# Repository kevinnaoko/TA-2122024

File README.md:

# TA-2122024
Capstone Design Kelompok 24

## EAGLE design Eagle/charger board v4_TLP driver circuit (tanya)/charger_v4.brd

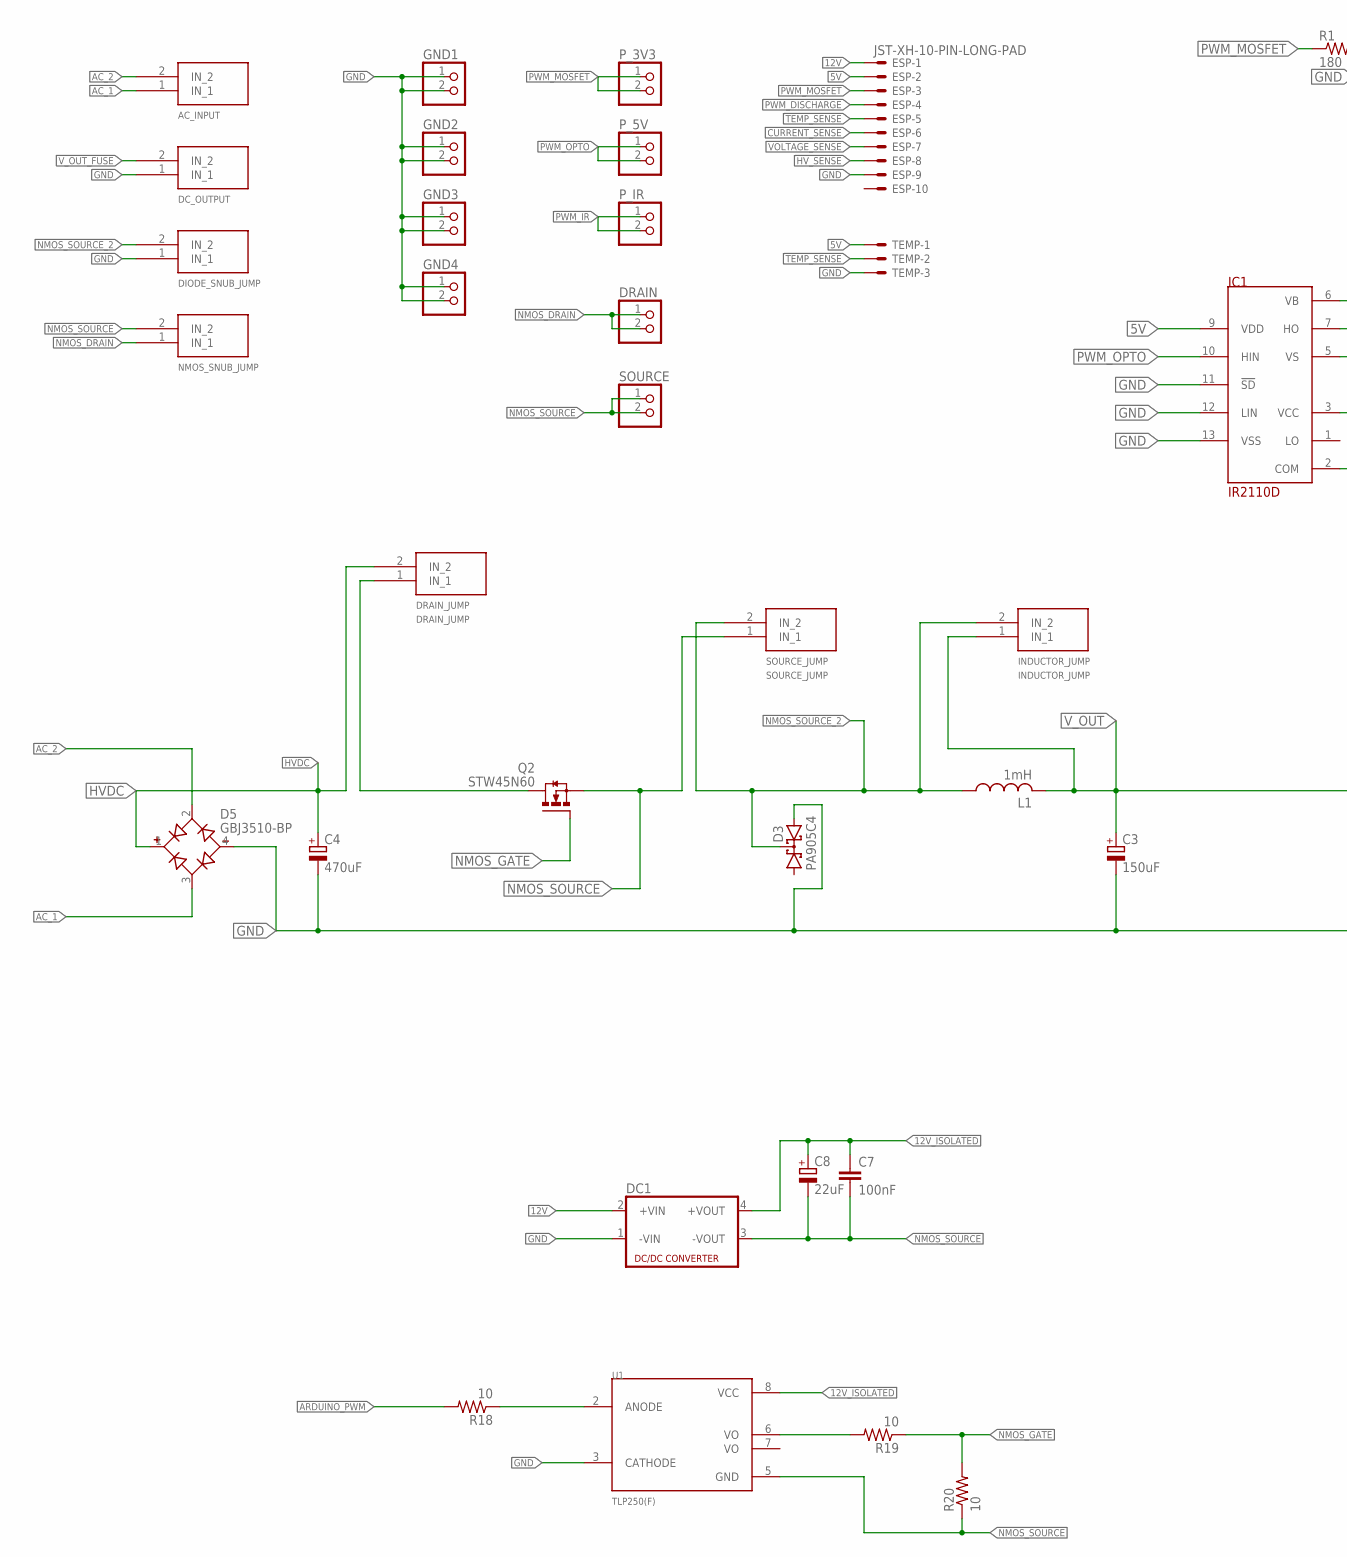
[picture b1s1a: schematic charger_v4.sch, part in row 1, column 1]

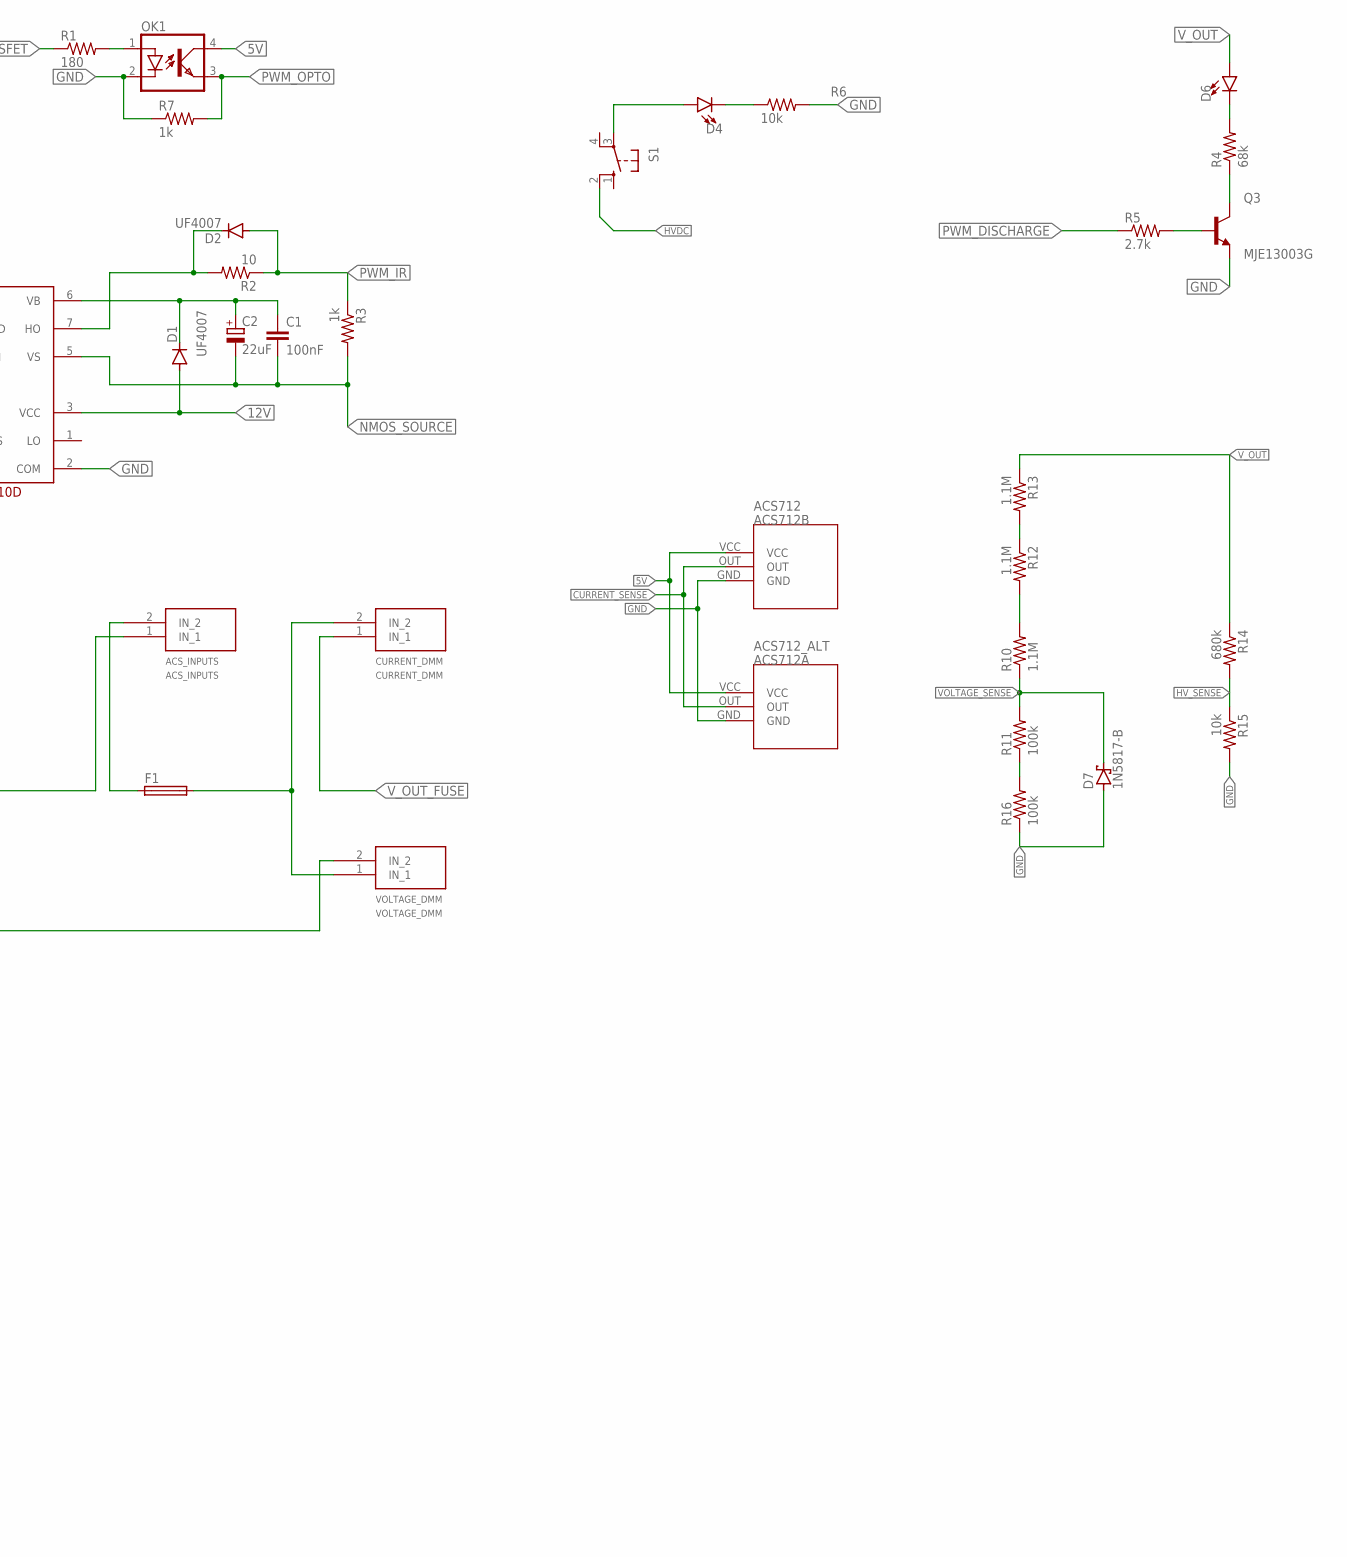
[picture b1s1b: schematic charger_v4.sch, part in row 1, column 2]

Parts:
ACS712: ACS712B; ACS712-2
ACS712_ALT: ACS712A; ACS712-1
ACS_INPUTS: ACS_INPUTS; TERMINAL_2P
AC_INPUT: AC_INPUT; TERMINAL_2P
C1, C7: 100nF; C025-025X050
C2, C8: 22uF; E2,5-6E
C3: 150uF; E7,5-18
C4: 470uF; EB35D
CURRENT_DMM: CURRENT_DMM; TERMINAL_2P
D1, D2: UF4007; DO34-7
D3: PA905C4; SOT93S
D4, D6: LED5MM; LED_5MM
D5: GBJ3510-BP; DIOB_GBJ3510-BP
D7: 1N5817-B; DO41-7.6
DC1: NME
DC_OUTPUT: DC_OUTPUT; TERMINAL_2P
DIODE_SNUB_JUMP: DIODE_SNUB_JUMP; TERMINAL_2P
DRAIN: PINHD-1X2; 1X02
DRAIN_JUMP: DRAIN_JUMP; TERMINAL_2P
ESP: JST-XH-10-PIN-LONG-PAD; JST-XH-10-PACKAGE-LONG-PAD
F1: FUSEHOLDER
GND1, GND2, GND3, GND4: PINHD-1X2; 1X02
IC1: IR2110D; DIL14
INDUCTOR_JUMP: INDUCTOR_JUMP; TERMINAL_2P
L1: 1mH; TJ7-U1
NMOS_SNUB_JUMP: NMOS_SNUB_JUMP; TERMINAL_2P
OK1: SFH618A-5; DIP4
P_3V3, P_5V: PINHD-1X2; 1X02
P_IR: PINHD-1X2; 1X02
Q2: STW45N60; TO247AC
Q3: MJE13003G; TO229P780X300X1364-3
R1: 180; 0204/7
R2, R18, R19, R20: 10; 0204/7
R3, R7: 1k; 0204/7
R4: 68k; 0411/15
R5: 2.7k; 0204/7
R6: 10k; 0204/7
R10, R12, R13: 1.1M; R0805
R11, R16: 100k; R0805
R14: 680k; 0207/10
R15: 10k; 0207/10
S1: 10-XX; B3F-10XX
SOURCE: PINHD-1X2; 1X02
SOURCE_JUMP: SOURCE_JUMP; TERMINAL_2P
TEMP: JST-XH-03-PIN-LONG-PAD; JST-XH-03-PACKAGE-LONG-PAD
U1: TLP250(F); DIP1016W50P254L966H380Q8P
VOLTAGE_DMM: VOLTAGE_DMM; TERMINAL_2P

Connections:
5V: ACS712.VCC, ACS712_ALT.VCC, ESP.2, IC1.9 (VDD), OK1.4 (COL), TEMP.1
12V: D1.A, DC1.2 (+VIN), ESP.1, IC1.3 (VCC)
12V_ISOLATED: C7.1, C8.+, DC1.4 (+VOUT), U1.8 (VCC)
AC_1: AC_INPUT.1 (IN_1), D5.3 (AC2)
AC_2: AC_INPUT.2 (IN_2), D5.2 (AC1)
ARDUINO_PWM: R18.2
CURRENT_SENSE: ACS712.OUT, ACS712_ALT.OUT, ESP.6
GND: ACS712.GND, ACS712_ALT.GND, C3.-, C4.-, D3.A2, D5.4 (-), D7.A, DC1.1 (-VIN), DC_OUTPUT.1 (IN_1), DIODE_SNUB_JUMP.1 (IN_1), ESP.9, GND1.1, GND1.2, GND2.1, GND2.2, GND3.1, GND3.2, GND4.1, GND4.2, IC1.2 (COM), IC1.11 (!SD), IC1.12 (LIN), IC1.13 (VSS), OK1.2 (C), Q3.3 (E), R6.2, R7.1, R15.2, R16.1, TEMP.3, U1.3 (CATHODE), VOLTAGE_DMM.2 (IN_2)
HVDC: C4.+, D5.1 (+), DRAIN_JUMP.2 (IN_2), S1.2 (S1)
HV_SENSE: ESP.8, R14.2, R15.1
unnamed: D2.C, IC1.7 (HO), R2.2
unnamed: D4.A, S1.3
unnamed: Q3.2 (C), R4.1
unnamed: D6.K (C), R4.2
unnamed: Q3.1 (B), R5.2
unnamed: D4.K (C), R6.1
unnamed: OK1.1 (A), R1.2
unnamed: CURRENT_DMM.2 (IN_2), F1.2, VOLTAGE_DMM.1 (IN_1)
unnamed: R10.2, R12.2
unnamed: R12.1, R13.2
unnamed: R11.1, R16.2
unnamed: ACS_INPUTS.2 (IN_2), F1.1
unnamed: R18.1, U1.2 (ANODE)
unnamed: R19.2, U1.6 (VO)
NMOS_DRAIN: DRAIN.1, DRAIN.2, DRAIN_JUMP.1 (IN_1), NMOS_SNUB_JUMP.1 (IN_1), Q2.2 (D)
NMOS_GATE: Q2.1 (G), R19.1, R20.2
NMOS_SOURCE: C1.2, C2.-, C7.2, C8.-, DC1.3 (-VOUT), IC1.5 (VS), NMOS_SNUB_JUMP.2 (IN_2), Q2.3 (S), R3.2, R20.1, SOURCE.1, SOURCE.2, SOURCE_JUMP.1 (IN_1), U1.5 (GND)
NMOS_SOURCE_2: D3.C, DIODE_SNUB_JUMP.2 (IN_2), INDUCTOR_JUMP.2 (IN_2), L1.1, SOURCE_JUMP.2 (IN_2)
PWM_DISCHARGE: ESP.4, R5.1
PWM_IR: D2.A, P_IR.1, P_IR.2, R2.1, R3.1
PWM_MOSFET: ESP.3, P_3V3.1, P_3V3.2, R1.1
PWM_OPTO: IC1.10 (HIN), OK1.3 (EMIT), P_5V.1, P_5V.2, R7.2
TEMP_SENSE: ESP.5, TEMP.2
VB: C1.1, C2.+, D1.C, IC1.6 (VB)
VOLTAGE_SENSE: D7.C, ESP.7, R10.1, R11.2
V_OUT: ACS_INPUTS.1 (IN_1), C3.+, D6.A, INDUCTOR_JUMP.1 (IN_1), L1.2, R13.1, R14.1
V_OUT_FUSE: CURRENT_DMM.1 (IN_1), DC_OUTPUT.2 (IN_2)

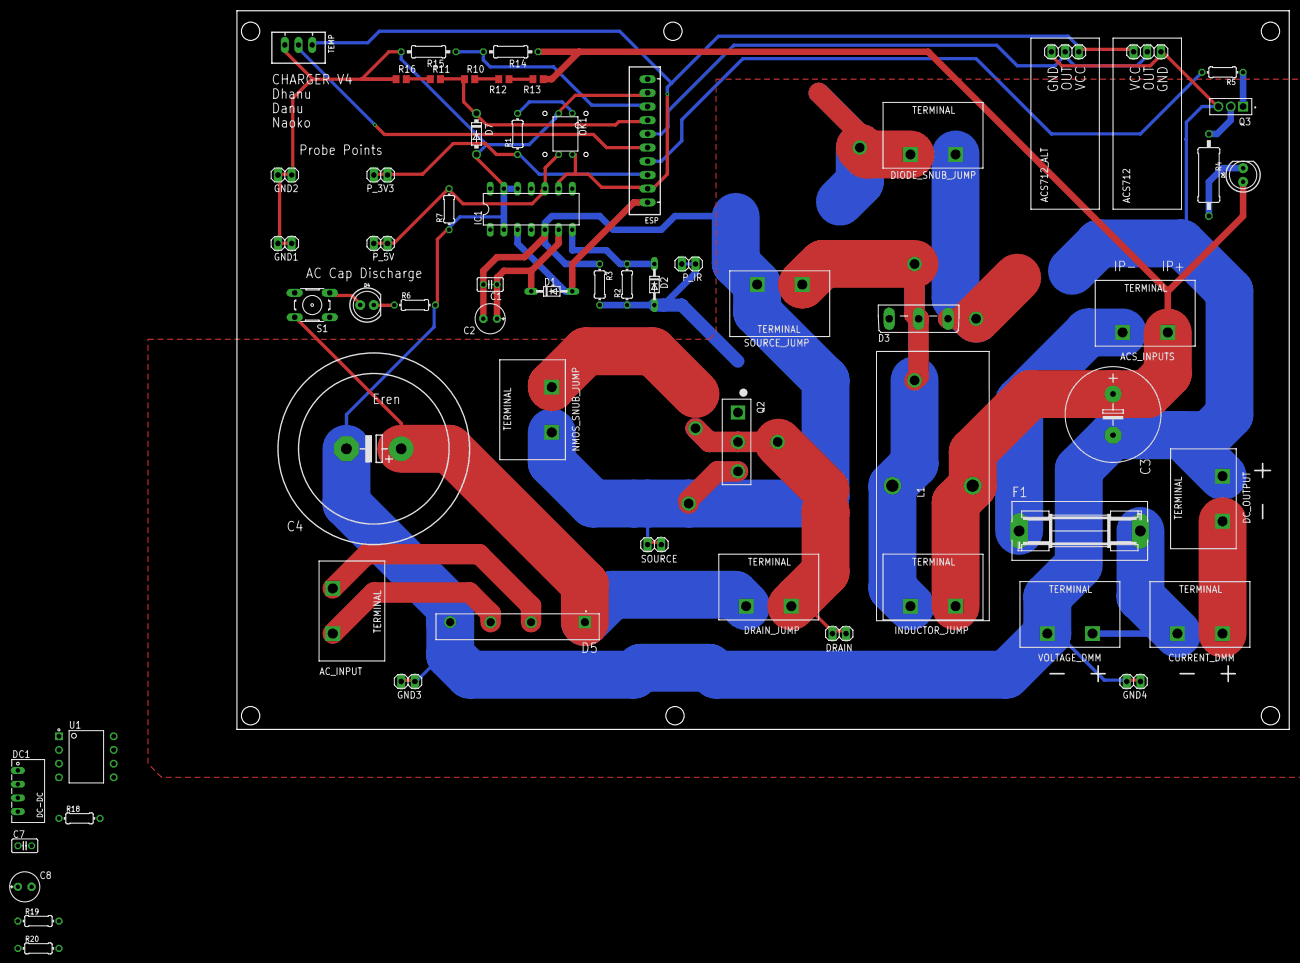
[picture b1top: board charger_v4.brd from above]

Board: 2 copper layers, 195.2 x 133.3 mm, 62 parts (0 on the bottom side), 36 nets.

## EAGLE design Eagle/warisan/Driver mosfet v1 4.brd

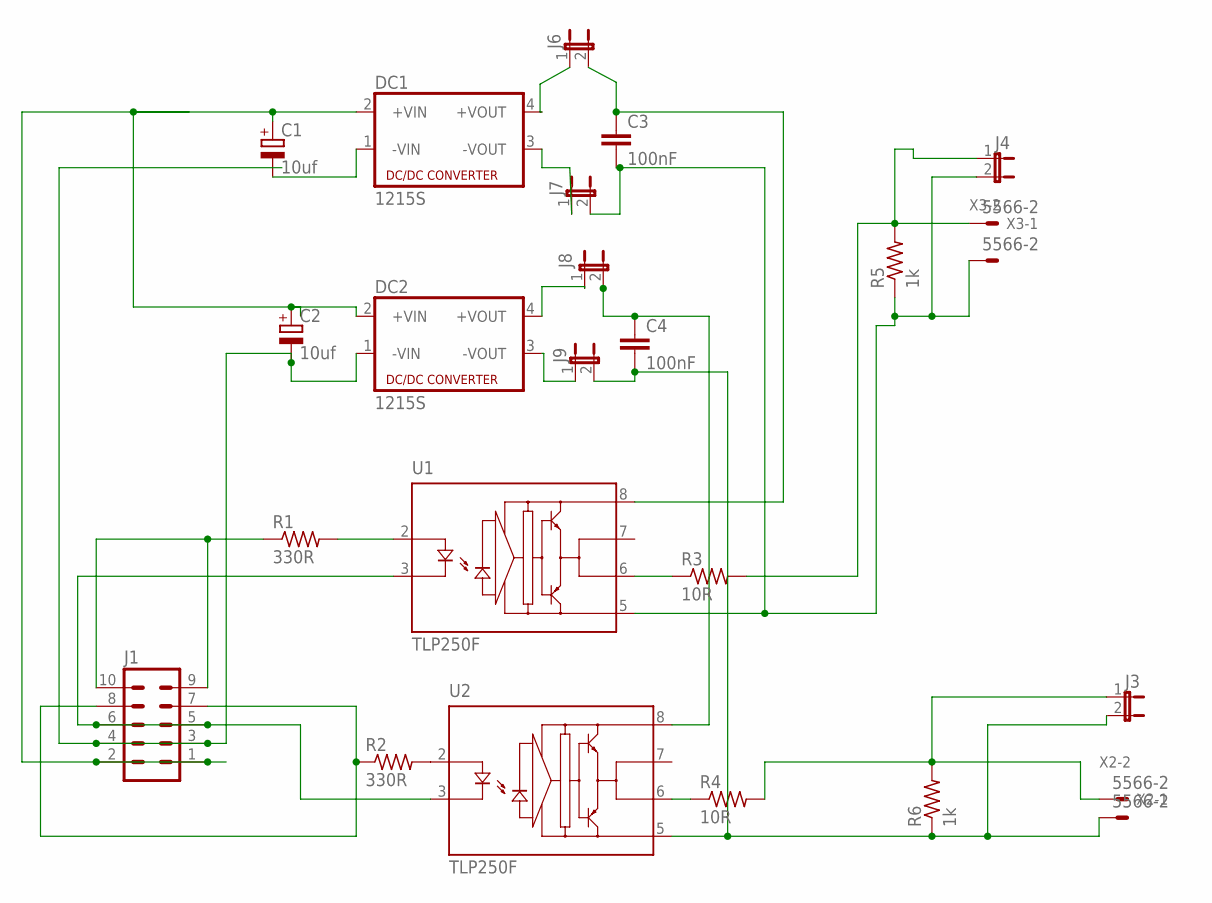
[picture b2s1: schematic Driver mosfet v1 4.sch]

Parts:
C1, C2: 10uf; E2,5-6
C3, C4: 100nF; C5B3.5
DC1, DC2: 1215S; 4SIL
J1: MA05-2
J3, J4, J6, J7, J8, J9: JP1E; JP1
R1, R2: 330R; 0309/12
R3, R4: 10R; 0309/12
R5, R6: 1k; 0309/12
U1, U2: TLP250F; DIL08
X2, X3: 5566-2

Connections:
unnamed: R2.2, U2.2 (A)
unnamed: C4.1, J8.2, U2.8 (VCC)
unnamed: C1.+, C2.+, DC1.2 (+VIN), DC2.2 (+VIN), J1.1, J1.2
unnamed: R4.1, U2.6 (VO)
unnamed: C3.1, J6.2, U1.8 (VCC)
unnamed: DC1.4 (+VOUT), J6.1
unnamed: R3.1, U1.6 (VO)
unnamed: R1.2, U1.2 (A)
unnamed: J1.9, J1.10, R1.1
unnamed: DC2.4 (+VOUT), J8.1
unnamed: C3.2, J4.2, J7.2, R5.1, U1.5 (GND), X3.2
unnamed: J1.5, J1.6, U1.3 (K), U2.3 (K)
unnamed: J4.1, R3.2, R5.2, X3.1
unnamed: J3.1, R4.2, R6.2, X2.1
unnamed: C4.2, J3.2, J9.2, R6.1, U2.5 (GND), X2.2
unnamed: J1.7, J1.8, R2.1
unnamed: C1.-, C2.-, DC1.1 (-VIN), DC2.1 (-VIN), J1.3, J1.4
unnamed: DC1.3 (-VOUT), J7.1
unnamed: DC2.3 (-VOUT), J9.1

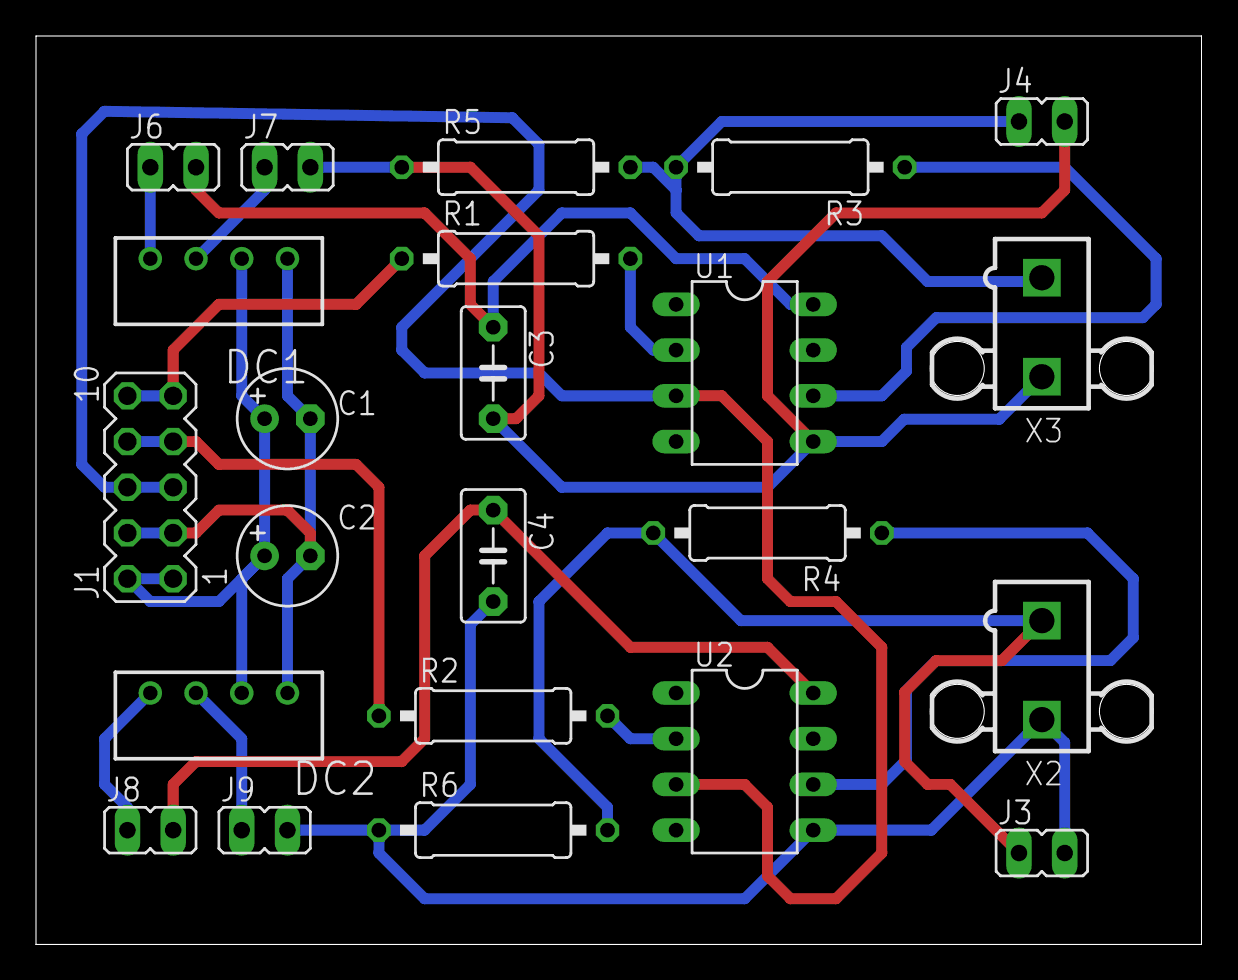
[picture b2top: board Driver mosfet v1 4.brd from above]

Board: 2 copper layers, 64.8 x 50.5 mm, 23 parts (0 on the bottom side), 19 nets.

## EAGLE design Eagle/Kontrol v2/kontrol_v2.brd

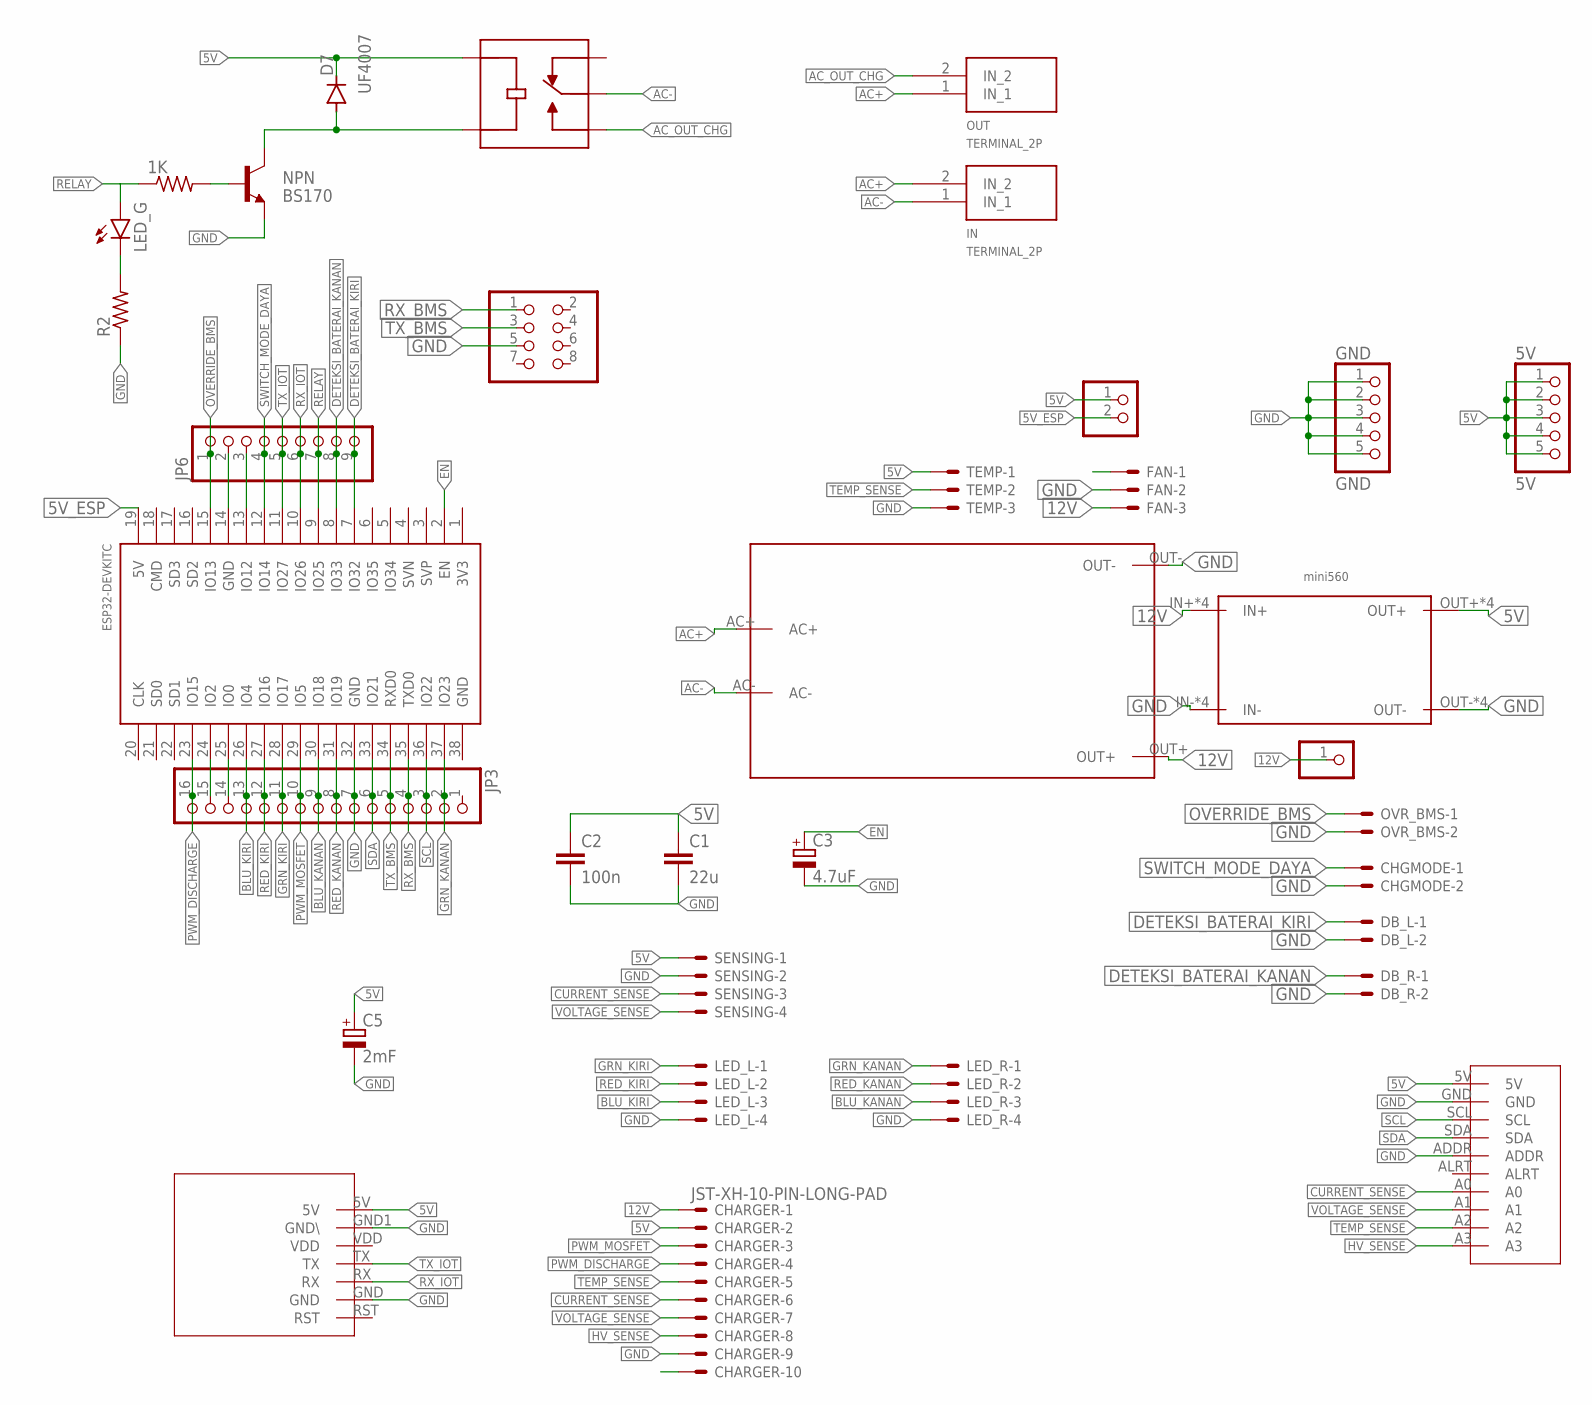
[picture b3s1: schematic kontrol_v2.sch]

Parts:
1K: 1k; 0204/7
5V: 5V; 1X05
C1: 22u; C2.5-5
C2: 100n; C2.5-6
C3: 4.7uF; E2,5-6E
C5: 2mF; E3,5-10
CHARGER: JST-XH-10-PIN-LONG-PAD; JST-XH-10-PACKAGE-LONG-PAD
CHGMODE: JST-XH-02-PIN-LONG-PAD; JST-XH-02-PACKAGE-LONG-PAD
D4: LED_G; LED_5MM
D7: UF4007; DO34-7
DB_L: JST-XH-02-PIN-LONG-PAD; JST-XH-02-PACKAGE-LONG-PAD
DB_R: JST-XH-02-PIN-LONG-PAD; JST-XH-02-PACKAGE-LONG-PAD
FAN: JST-XH-03-PIN-LONG-PAD; JST-XH-03-PACKAGE-LONG-PAD
GND: GND; 1X05
HI_LINK1: HI_LINK
IN: TERMINAL_2P
JP2: PINHD-2X4; 2X04
JP3: PINHD-1X16; 1X16
JP4: PINHD-1X1; 1X01
JP6: PINHD-1X9; 1X09
JP7: PINHD-1X2; 1X02
K1: SRD-12VDC-SL-C; RELAY_SRD-12VDC-SL-C
LED_L: JST-XH-04-PIN-LONG-PAD; JST-XH-04-PACKAGE-LONG-PAD
LED_R: JST-XH-04-PIN-LONG-PAD; JST-XH-04-PACKAGE-LONG-PAD
MINI1: MINI560
NPN: BS170; TO92-CBE
OUT: TERMINAL_2P
OVR_BMS: JST-XH-02-PIN-LONG-PAD; JST-XH-02-PACKAGE-LONG-PAD
R2: 6k; 0204/7
SENSING: JST-XH-04-PIN-LONG-PAD; JST-XH-04-PACKAGE-LONG-PAD
TEMP: JST-XH-03-PIN-LONG-PAD; JST-XH-03-PACKAGE-LONG-PAD
U$1: ESP32DEVKITC; ESP32-DEVKITC
U$2: ADS1115
U$3: SIM800V2

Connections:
5V: 5V.1, 5V.2, 5V.3, 5V.4, 5V.5, C1.1, C2.1, C5.+, CHARGER.2, D7.C, JP7.1, K1.COIL1, MINI1.OUT+, MINI1.OUT+1 (OUT+), MINI1.OUT+2 (OUT+), MINI1.OUT+3 (OUT+), SENSING.1, TEMP.1, U$2.5V, U$3.5V
5V_ESP: JP7.2, U$1.19 (5V)
12V: CHARGER.1, FAN.3, HI_LINK1.OUT+, JP4.1, MINI1.IN+, MINI1.IN+1 (IN+), MINI1.IN+2 (IN+), MINI1.IN+3 (IN+)
AC+: HI_LINK1.AC+, IN.2 (IN_2), OUT.1 (IN_1)
AC-: HI_LINK1.AC-, IN.1 (IN_1), K1.COM
AC_OUT_CHG: K1.NO, OUT.2 (IN_2)
BLU_KANAN: JP3.9, LED_R.3, U$1.30 (IO18)
BLU_KIRI: JP3.13, LED_L.3, U$1.26 (IO4)
CURRENT_SENSE: CHARGER.6, SENSING.3, U$2.A0
DETEKSI_BATERAI_KANAN: DB_R.1, JP6.8, U$1.8 (IO33)
DETEKSI_BATERAI_KIRI: DB_L.1, JP6.9, U$1.7 (IO32)
EN: C3.+, U$1.2 (EN)
GND: C1.2, C2.2, C3.-, C5.-, CHARGER.9, CHGMODE.2, DB_L.2, DB_R.2, FAN.2, GND.1, GND.2, GND.3, GND.4, GND.5, HI_LINK1.OUT-, JP2.5, JP3.7, LED_L.4, LED_R.4, MINI1.IN-, MINI1.IN-1 (IN-), MINI1.IN-2 (IN-), MINI1.IN-3 (IN-), MINI1.OUT-, MINI1.OUT-1 (OUT-), MINI1.OUT-2 (OUT-), MINI1.OUT-3 (OUT-), NPN.E, OVR_BMS.2, R2.1, SENSING.2, TEMP.3, U$1.32 (GND), U$2.ADDR, U$2.GND, U$3.GND, U$3.GND1 (GND\)
GRN_KANAN: JP3.2, LED_R.1, U$1.37 (IO23)
GRN_KIRI: JP3.11, LED_L.1, U$1.28 (IO17)
HV_SENSE: CHARGER.8, U$2.A3
unnamed: D4.K (C), R2.2
unnamed: JP6.2, U$1.14 (GND)
unnamed: JP6.3, U$1.13 (IO12)
unnamed: 1K.2, NPN.B
unnamed: D7.A, K1.COIL2, NPN.C
unnamed: JP3.14, U$1.25 (IO0)
unnamed: JP3.15, U$1.24 (IO2)
OVERRIDE_BMS: JP6.1, OVR_BMS.1, U$1.15 (IO13)
PWM_DISCHARGE: CHARGER.4, JP3.16, U$1.23 (IO15)
PWM_MOSFET: CHARGER.3, JP3.10, U$1.29 (IO5)
RED_KANAN: JP3.8, LED_R.2, U$1.31 (IO19)
RED_KIRI: JP3.12, LED_L.2, U$1.27 (IO16)
RELAY: 1K.1, D4.A, JP6.7, U$1.9 (IO25)
RX_BMS: JP2.1, JP3.4, U$1.35 (TXD0)
RX_IOT: JP6.6, U$1.10 (IO26), U$3.RX
SCL: JP3.3, U$1.36 (IO22), U$2.SCL
SDA: JP3.6, U$1.33 (IO21), U$2.SDA
SWITCH_MODE_DAYA: CHGMODE.1, JP6.4, U$1.12 (IO14)
TEMP_SENSE: CHARGER.5, TEMP.2, U$2.A2
TX_BMS: JP2.3, JP3.5, U$1.34 (RXD0)
TX_IOT: JP6.5, U$1.11 (IO27), U$3.TX
VOLTAGE_SENSE: CHARGER.7, SENSING.4, U$2.A1

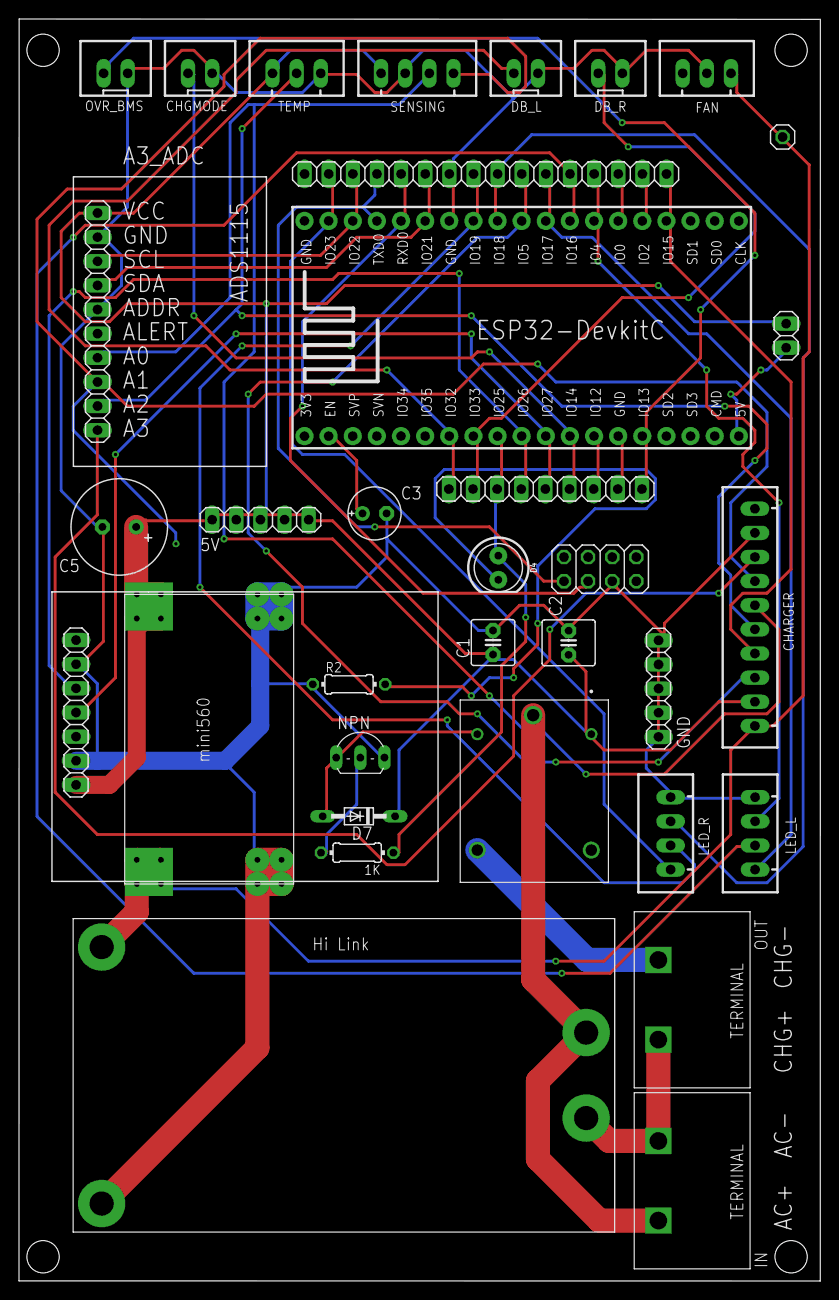
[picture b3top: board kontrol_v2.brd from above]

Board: 2 copper layers, 84.3 x 132.8 mm, 34 parts (0 on the bottom side), 38 nets.

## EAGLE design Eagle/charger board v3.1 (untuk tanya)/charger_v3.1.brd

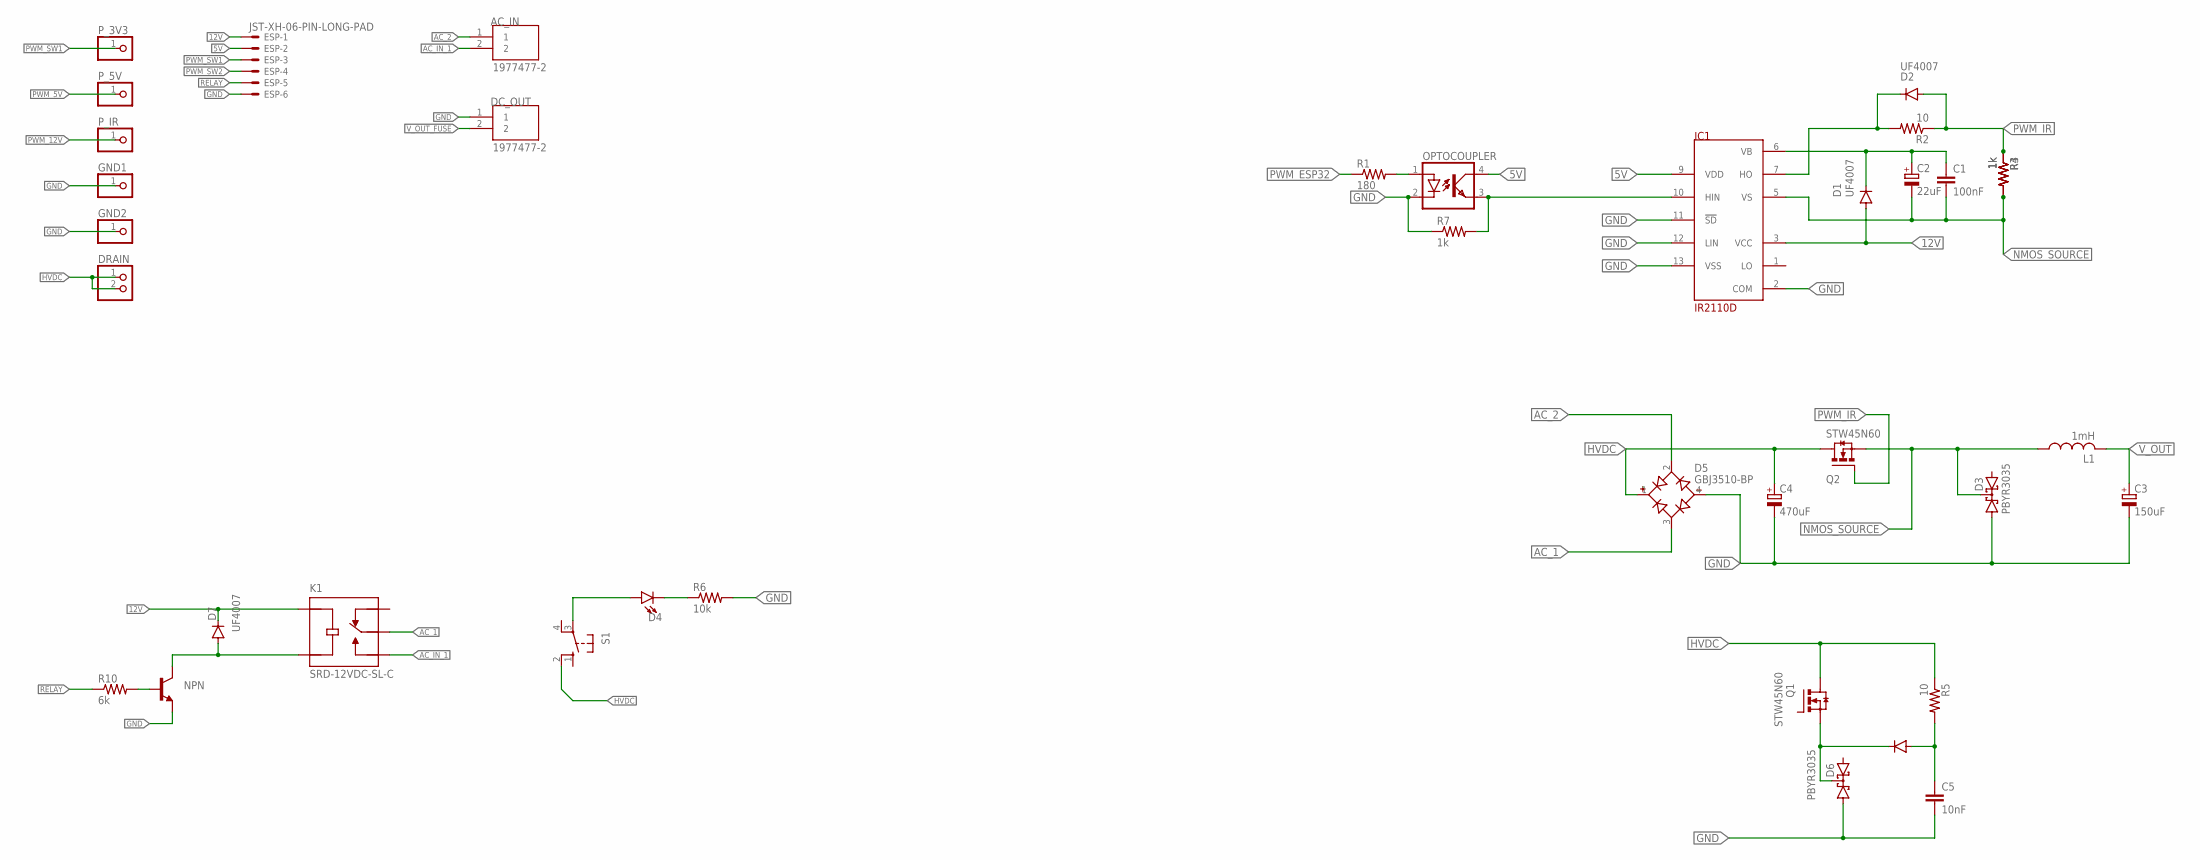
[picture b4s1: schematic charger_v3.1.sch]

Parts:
AC_IN: 1977477-2; TE_1977477-2
C1: 100nF; C025-025X050
C2: 22uF; E2,5-6E
C3: 150uF; E7,5-18
C4: 470uF; EB35D
C5: 10nF; C025-025X050
D1, D2, D7: UF4007; DO34-7
D3, D6: PBYR3035; SOT93S
D4: LED5MM; LED_5MM
D5: GBJ3510-BP; DIOB_GBJ3510-BP
D8: 1N4148DO35-7; DO35-7
DC_OUT: 1977477-2; TE_1977477-2
DRAIN: PINHD-1X2; 1X02
ESP: JST-XH-06-PIN-LONG-PAD; JST-XH-06-PACKAGE-LONG-PAD
GND1, GND2: PINHD-1X1; 1X01
IC1: IR2110D; DIL14
K1: SRD-12VDC-SL-C; RELAY_SRD-12VDC-SL-C
L1: 1mH; TJ7-U1
NPN: BC547A-NPN-TO92-CBE; TO92-CBE
OPTOCOUPLER: SFH618A-5; DIP4
P_3V3, P_5V: PINHD-1X1; 1X01
P_IR: PINHD-1X1; 1X01
Q1, Q2: STW45N60; TO247AC
R1: 180; 0204/7
R2, R5: 10; 0204/7
R3, R4, R7: 1k; 0204/7
R6: 10k; 0204/7
R10: 6k; 0204/7
S1: 10-XX; B3F-10XX

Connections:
5V: ESP.2, IC1.9 (VDD), OPTOCOUPLER.4 (COL)
12V: D1.A, D7.C, ESP.1, IC1.3 (VCC), K1.COIL1
AC_1: D5.3 (AC2), K1.COM
AC_2: AC_IN.1, D5.2 (AC1)
AC_IN_1: AC_IN.2, K1.NO
GND: C3.-, C4.-, D3.A1, D5.4 (-), DC_OUT.1, ESP.6, GND1.1, GND2.1, IC1.2 (COM), IC1.11 (!SD), IC1.12 (LIN), IC1.13 (VSS), NPN.E, OPTOCOUPLER.2 (C), R6.2, R7.1
HVDC: C4.+, D5.1 (+), DRAIN.1, DRAIN.2, Q2.2 (D), S1.2 (S1)
unnamed: D2.C, IC1.7 (HO), R2.2
unnamed: D4.A, S1.3
unnamed: C5.2, D6.A1
unnamed: D6.C, D8.C, Q1.3 (S)
unnamed: Q1.2 (D), R5.1
unnamed: C5.1, D8.A, R5.2
unnamed: D4.K (C), R6.1
unnamed: OPTOCOUPLER.1 (A), R1.2
unnamed: NPN.B, R10.2
unnamed: D7.A, K1.COIL2, NPN.C
NMOS_SOURCE: C1.2, C2.-, D3.C, IC1.5 (VS), L1.1, Q2.3 (S), R3.2, R4.2
PWM_5V: IC1.10 (HIN), OPTOCOUPLER.3 (EMIT), P_5V.1, R7.2
PWM_12V: P_IR.1
PWM_ESP32: R1.1
PWM_IR: D2.A, Q2.1 (G), R2.1, R3.1, R4.1
PWM_SW1: ESP.3, P_3V3.1
PWM_SW2: ESP.4
RELAY: ESP.5, R10.1
VB: C1.1, C2.+, D1.C, IC1.6 (VB)
V_OUT: C3.+, L1.2
V_OUT_FUSE: DC_OUT.2

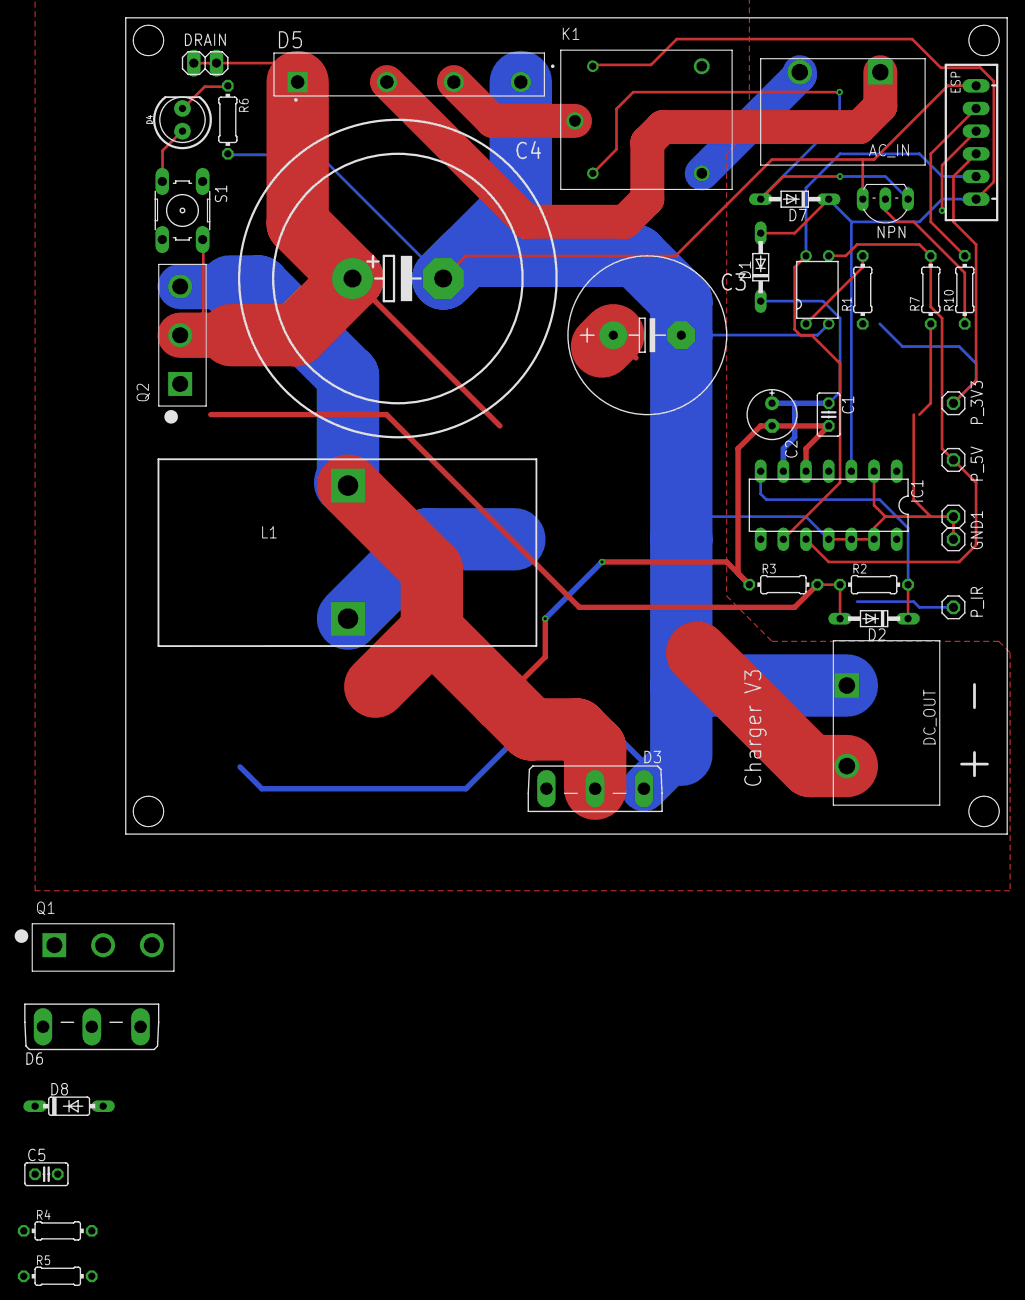
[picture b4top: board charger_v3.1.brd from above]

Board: 2 copper layers, 98.7 x 91.4 mm, 38 parts (0 on the bottom side), 24 nets.

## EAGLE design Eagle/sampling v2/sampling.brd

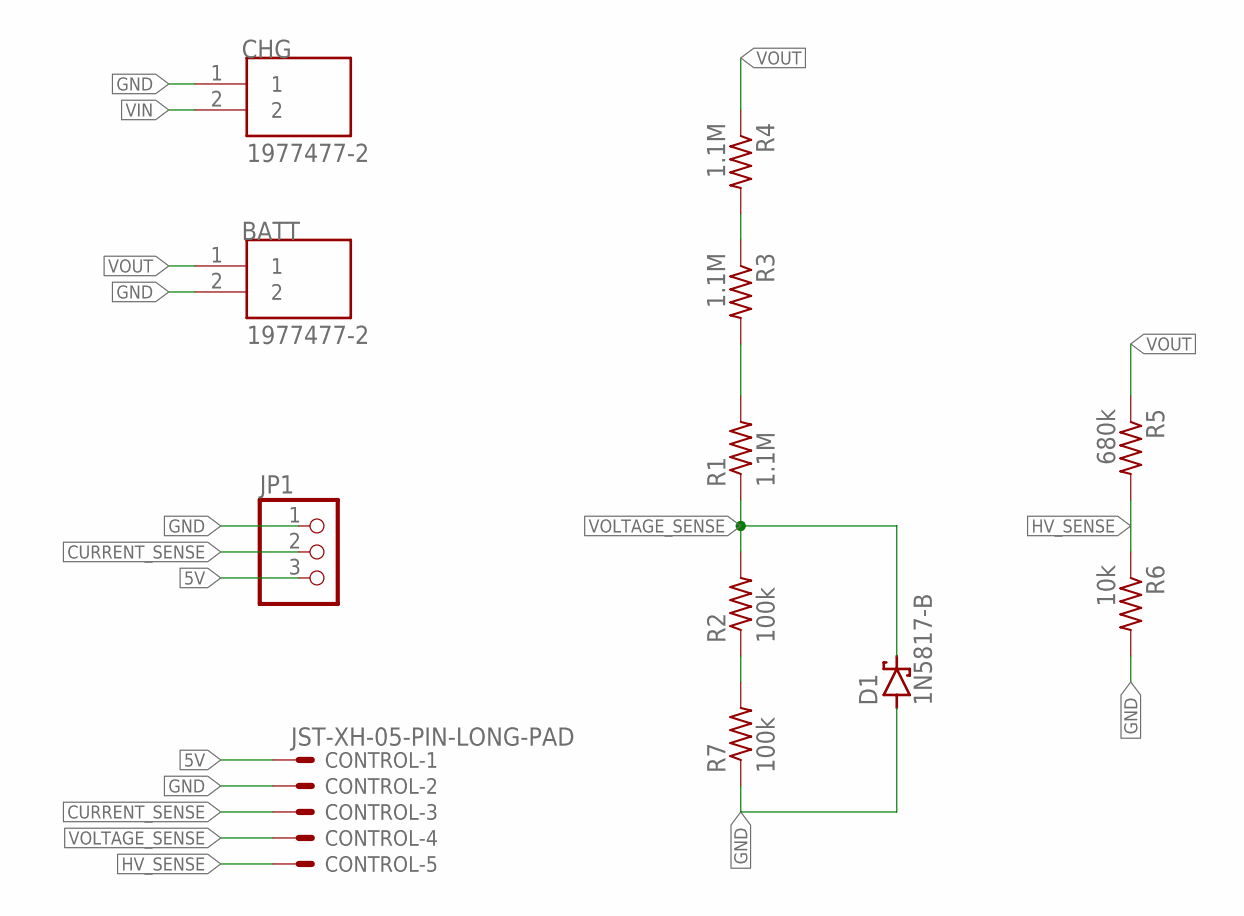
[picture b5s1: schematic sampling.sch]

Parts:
BATT: 1977477-2; TE_1977477-2
CHG: 1977477-2; TE_1977477-2
CONTROL: JST-XH-05-PIN-LONG-PAD; JST-XH-05-PACKAGE-LONG-PAD
D1: 1N5817-B; DO41-7.6
JP1: PINHD-1X3; 1X03
R1, R3, R4: 1.1M; R0805
R2, R7: 100k; R0805
R5: 680k; 0207/10
R6: 10k; 0207/10

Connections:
5V: CONTROL.1, JP1.3
CURRENT_SENSE: CONTROL.3, JP1.2
GND: BATT.2, CHG.1, CONTROL.2, D1.A, JP1.1, R6.2, R7.1
HV_SENSE: CONTROL.5, R5.2, R6.1
unnamed: R1.2, R3.2
unnamed: R3.1, R4.2
unnamed: R2.1, R7.2
VIN: CHG.2
VOLTAGE_SENSE: CONTROL.4, D1.C, R1.1, R2.2
VOUT: BATT.1, R4.1, R5.1

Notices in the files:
parts and their libraries:
Sparkfun_LED: Licensing: Creative Commons ShareAlike 4.0 International - https://creativecommons.org/licenses/by-sa/4.0
